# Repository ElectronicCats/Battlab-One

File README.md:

# BattLab-One
The BattLab-One estimates the battery life of your IOT project using the DUT cutoff voltage, battery state of charge data, event duration, and captured active and sleep event current profiles.

## Main characteristics 

- Captures both active event and sleep mode current

- MSP430 microcontroller based device that simulates standard batteries for Li-Ion, LiFePO4, Alkaline, NiMh, NiCd

- Provides voltages of 1.2V, 1.5V, 2.4V, 3.0V, 3.2, 3.6V, 3.7V, 4.5V at up to 450 mA.

- Trigger input to capture firmware states and their impact on overall battery life

- 1kHz Sample rate, 16 bit delta-sigma ADC

- Long active event capture duration from seconds to hours

- Extremely low burden voltage across all ranges (BattLab-One provides PSU output)

- Provides “what-if” optimization by letting you change your battery, current profiles, active and sleep duration as well as cutoff voltage

- Features the ability to save profiles so you can compare your DUT current profiles

- Interactive/detailed active current plot so you can look for anomalies and identify performance

## Archives
  - Battlab-One Quick Start Guide

  - BattLab_One_Production_Rev_A.py - Python Application Code for Production version 1.01

  - Production_Rev_A.sch - Schematic in Kicad

  - Production_Rev_A.kicad_pcb- PCB Layout in Kicad 

  - MSP430Firmware.c - Firmware code for the MSP430 for Production Version 1.01

  - BOM_Production_Rev_A - Bill of Materials for Battlab-One Production Rev A

  - 98-bluebird-labs.rules - Linux udev rules for Battlab-One

  See more at www.bluebird-labs.com

## Development

This project uses pipenv to take care of setting up a virtual environment as well as managing the dependencies needed.

1. Install pipenv as describe here https://pypi.org/project/pipenv/
2. Start a terminal and change to the root folder of this project.
3. Run pipenv to setup the environment: `pipenv install --dev`
4. Start the pipenv shell: `pipenv shell`
5. Start the application: `python BattLab_One_V1.0.6.py`

## License 

Electronic Cats invests time and resources providing this open source design, please support Electronic Cats and open-source hardware by purchasing products from Electronic Cats!

Designed by Bluebird Labs LLC

KiCad version Electronic Cats.

Electronic Cats is a registered trademark, please do not use if you sell these PCBs.

January 2021

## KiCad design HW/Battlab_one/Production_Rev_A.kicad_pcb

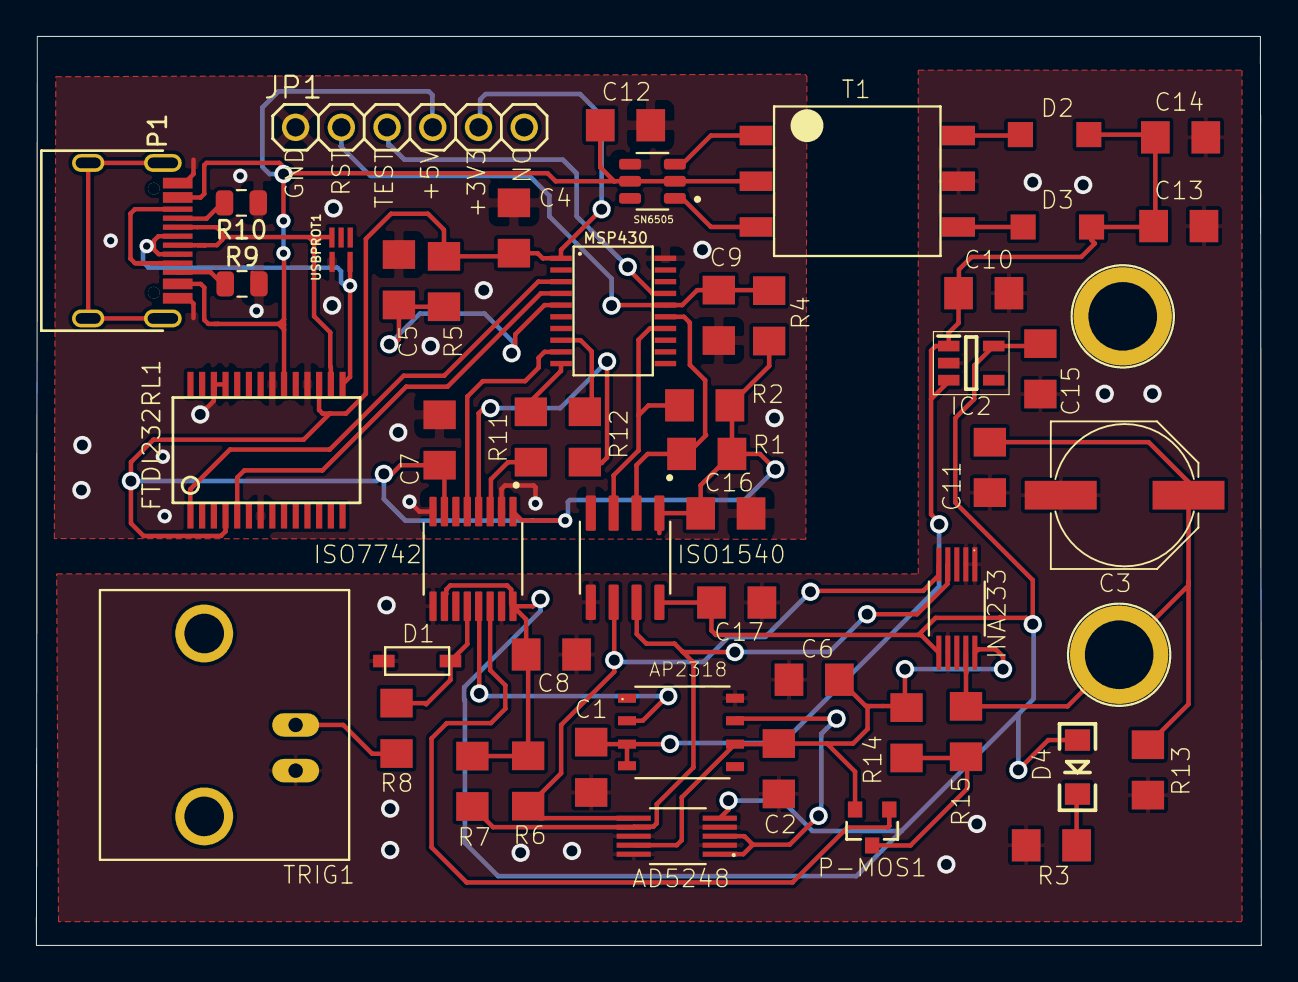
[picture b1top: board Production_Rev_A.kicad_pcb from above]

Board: 2 copper layers, 68.1 x 50.5 mm, 53 parts (0 on the bottom side), 37 nets.

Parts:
AD5248: 100K; MSOP-10
AP2318: AP2318; SOIC-8
C1, C4, C10: 1uF; 1206
C2, C6, C15: 2.2uF; 1206
C3: 1000uF; PANASONIC_F
C5: .1uF; 1206
C7, C8, C11, C14, C16, C17: 0.1uF; 1206
C9: 1nF; 1206
C12, C13: 10uF; 1206
D1: DIODESOD-123; SOD-123
D2, D3: MBR0520LT1G; SOD3716X117(SOD-123)
D4: BLUE; LED-1206
FTDI232RL1: FT232RL; SSOP28DB
IC2: MIC5225-5.0YM5-TR; SOT95P280X130-5N
INA233: INA233; VSSOP-10
ISO1540: ISO1540; SOIC127P600X175-8N
ISO7742: ISO7742DBQ; SOP63P599X175-16N
J1, J3: BANANA_CONN
JP1: PINHD-1X6; 1X06
MSP430: MSP430; PW20
P1: USB_C_Plug; C393939
P-MOS1: P-MOSFET; SOT23-3
R1, R2, R6, R7: 10K; 1206
R3: 470; 1206
R4, R5: 47K; 1206
R8, R14: 100; 1206
R9, R10: 5.1K; R_0805_2012Metric
R11, R12: 220; 1206
R13: 100k; 1206
R15: 0.1; 1206
SN6505: SN6505; SOT95P280X145-6N
T1: 750315371; TOR-6P-HT4_SMT_6PIN_(1201)
TRIG1: BNCPTH; BNC
USBPROT1: TPD2E2U06DRLR; SOT50P160X60-5N

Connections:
/D+: FTDI232RL1.15, P1.A6, USBPROT1.5
/D-: FTDI232RL1.16, P1.A7, USBPROT1.3
/VBUS: C12.1, FTDI232RL1.20, JP1.3, P1.A4, SN6505.2, SN6505.5, T1.2
GND: C4.1, C5.1, C7.1, C9.1, C12.2, C16.2, FTDI232RL1.7, FTDI232RL1.18, FTDI232RL1.21, FTDI232RL1.25, FTDI232RL1.26, ISO1540.4, ISO7742.2, ISO7742.8, JP1.6, MSP430.20, P1.A1, R9.2, R10.1, SN6505.4, USBPROT1.4
GND1: AD5248.2, AD5248.4, AD5248.8, AD5248.10, AP2318.8, C1.1, C2.2, C3.-, C6.2, C8.2, C10.2, C11.1, C13.2, C14.2, C15.2, C17.2, D1.A, IC2.2, INA233.1, INA233.2, INA233.7, ISO1540.5, ISO7742.9, ISO7742.15, J3.P$1, R3.1, R13.2, T1.5, TRIG1.GND
unnamed: AD5248.1, AD5248.3, AP2318.7
unnamed: AD5248.5, C8.1, C15.1, C17.1, D4.A, IC2.5, INA233.6, ISO1540.8, ISO7742.10, ISO7742.16, R6.1, R7.1
unnamed: AD5248.6, INA233.5, ISO1540.6, R6.2
unnamed: AD5248.7, INA233.4, ISO1540.7, R7.2
unnamed: AD5248.9, AP2318.6, C2.1, C6.1, INA233.10, P-MOS1.2, R14.1
unnamed: AP2318.2, ISO7742.13
unnamed: AP2318.3, AP2318.4, C1.2, C10.1, C13.1, C14.1, D2.1, D3.1, IC2.1, IC2.3
unnamed: C5.2, MSP430.5, R5.1
unnamed: C9.2, JP1.5, MSP430.16, R4.2
unnamed: C3.+, C11.2, INA233.9, J1.P$1, R13.1, R15.2
unnamed: C4.2, C7.2, C16.1, FTDI232RL1.4, FTDI232RL1.17, ISO1540.1, ISO7742.1, ISO7742.7, JP1.2, MSP430.1, R1.2, R2.2, R4.1, R5.2
unnamed: D1.C, ISO7742.12, R8.2
unnamed: D2.2, T1.6
unnamed: D3.2, T1.4
unnamed: D4.C, R3.2
unnamed: FTDI232RL1.1, MSP430.3
unnamed: FTDI232RL1.5, MSP430.4
unnamed: ISO1540.2, MSP430.15, R1.1
unnamed: ISO1540.3, MSP430.14, R2.1
unnamed: ISO7742.3, R11.2
unnamed: ISO7742.4, R12.2
unnamed: ISO7742.5, MSP430.9
unnamed: ISO7742.14, P-MOS1.1
unnamed: JP1.4, MSP430.17
unnamed: MSP430.8, R12.1
unnamed: MSP430.10, R11.1
unnamed: P1.A5, R10.2
unnamed: P1.B5, R9.1
unnamed: P-MOS1.3, R14.2, R15.1
unnamed: R8.1, TRIG1.S
unnamed: SN6505.1, T1.3
unnamed: SN6505.3, T1.1

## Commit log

2020-09-07 Eagle imported
2020-09-07 Type-C Usb and footprint assigned.
2020-09-07 UsbC routed
2020-09-07 USB-C resistor
2020-09-07 paht for eagle
2020-09-07 Usb c fixed RTC 0 unconnect
2020-09-07 Silkscreen moved
2020-11-26 manf#
2020-11-27 Added component
2020-12-14 Added other "FTDI" component
2021-01-29 erased eagle files
2021-01-29 Update and rename MIT License.txt to LICENSE
